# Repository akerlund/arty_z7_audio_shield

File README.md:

# arty_z7_audio_shield

Stereo audio IF with a Cirrus CS4272 24-bit codec IC.
Designed to be placed as a shield on the Arty Z7 FPGA board.
Has a 20-pin connector for the "mixer interface", i.e., a PCB with sliders and encoders.

First test (verison1) failed, the +-5V booster (bottom left in pic) operates incorrecty and
eats a lot of current, causing the 3.3V supply down to 0.8V.

Forgot the exposed thermal pad under that IC, too. Fixed with some copper tape, but might correlate?

Next step is to try a new design, i.e., another booster.

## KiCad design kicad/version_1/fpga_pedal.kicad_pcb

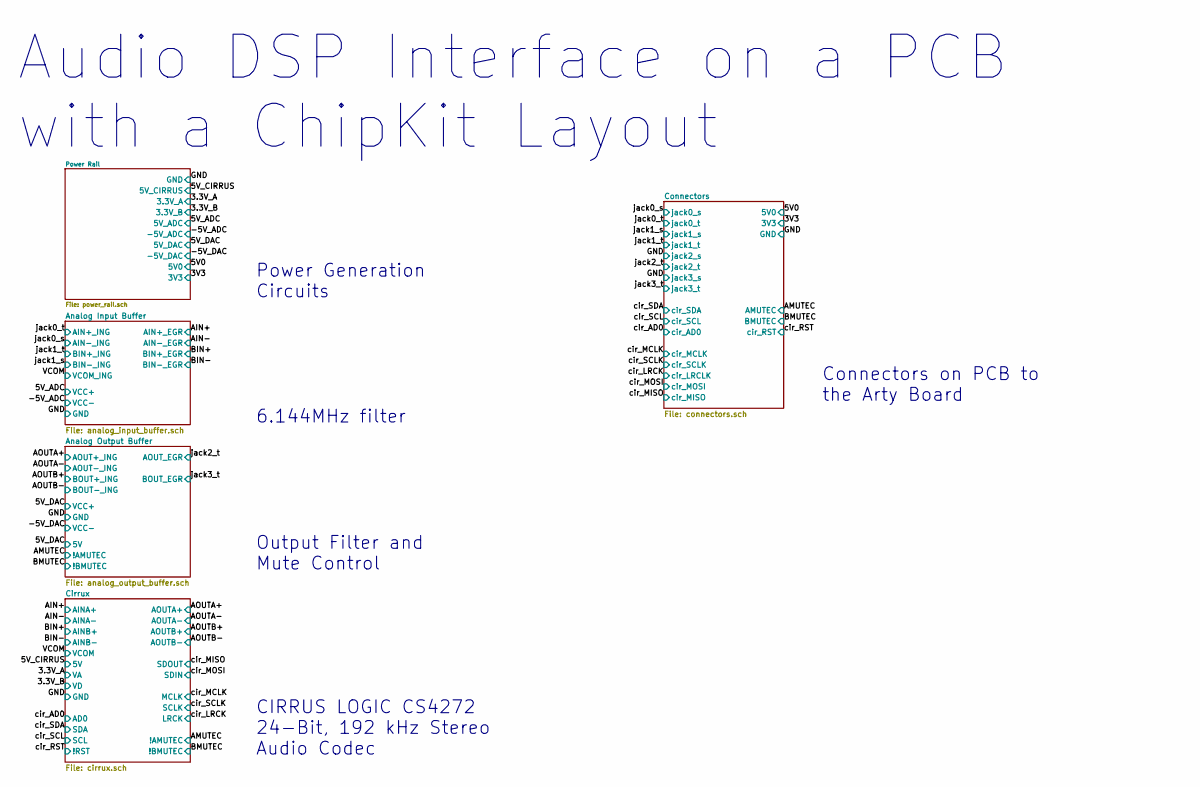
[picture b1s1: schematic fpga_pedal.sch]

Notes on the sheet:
CIRRUS LOGIC CS4272 24-Bit, 192 kHz Stereo Audio Codec
6.144MHz filter
Output Filter and Mute Control
Power Generation Circuits
Connectors on PCB to the Arty Board
Audio DSP Interface on a PCB with a ChipKit Layout

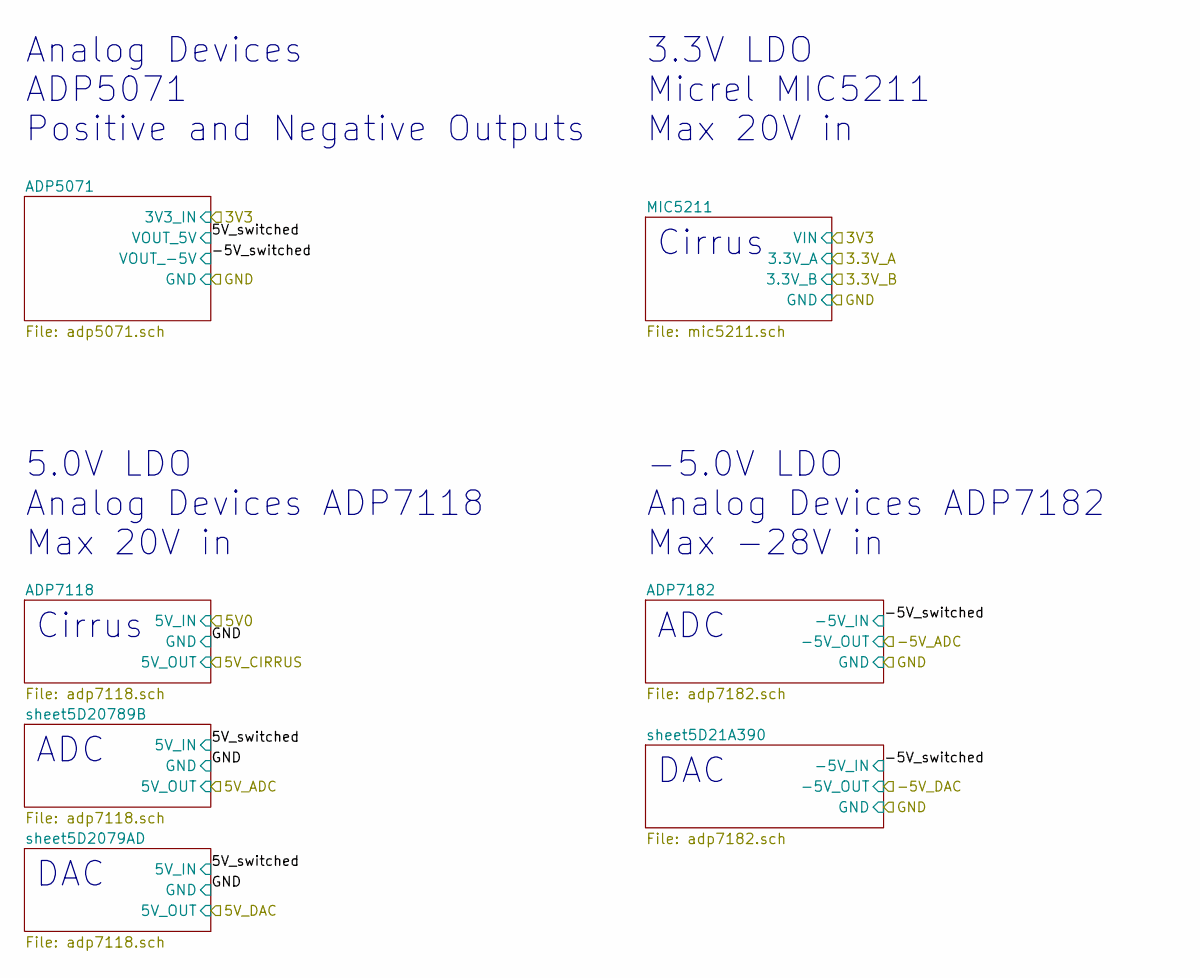
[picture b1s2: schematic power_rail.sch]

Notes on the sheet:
3.3V LDO Micrel MIC5211 Max 20V in
5.0V LDO Analog Devices ADP7118 Max 20V in
-5.0V LDO Analog Devices ADP7182 Max -28V in
Analog Devices ADP5071 Positive and Negative Outputs
ADC
Cirrus
DAC

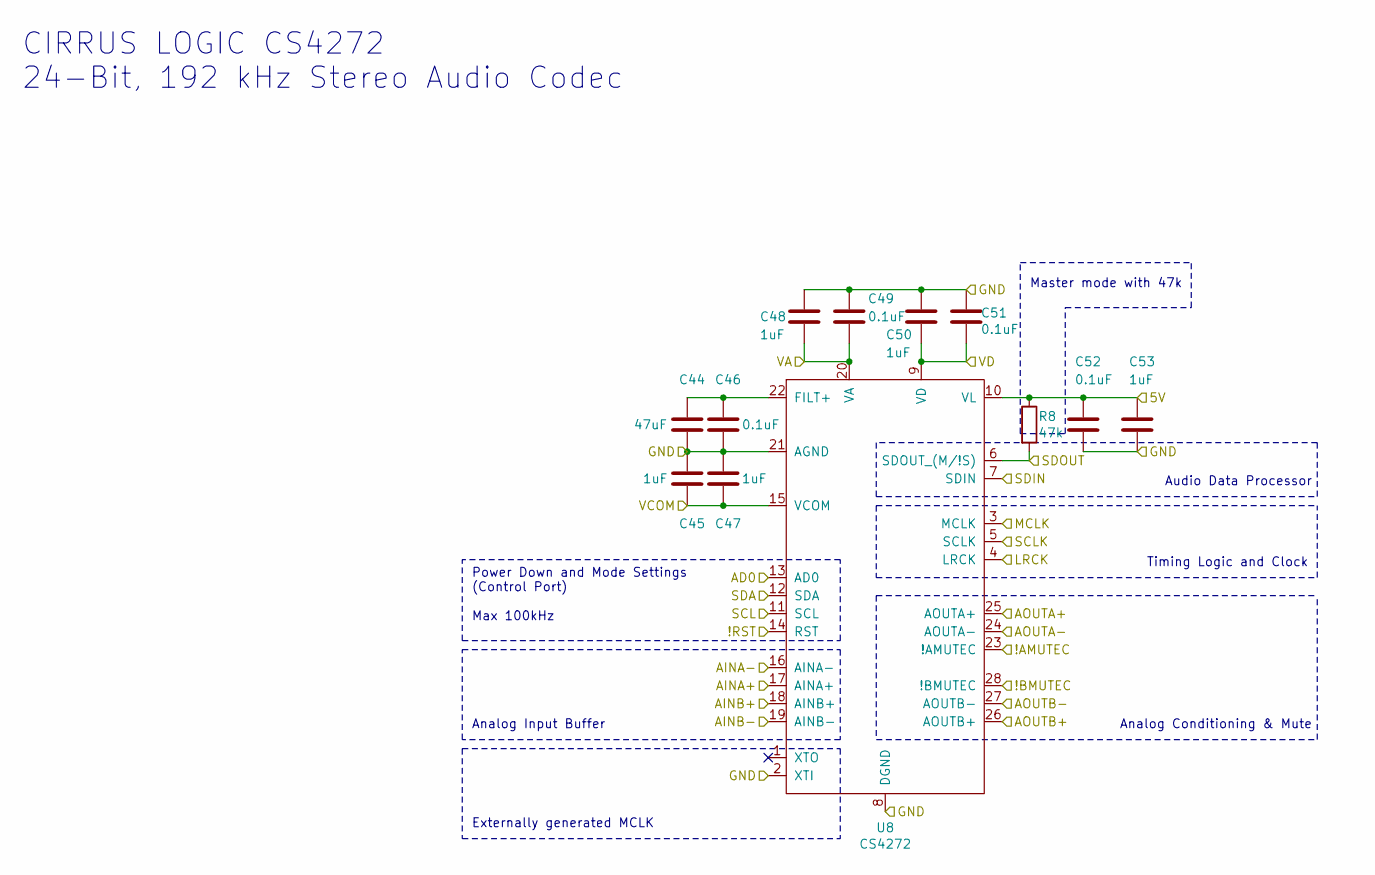
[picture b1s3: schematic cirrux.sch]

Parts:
C44: 47uF; C_1206_3216Metric_Pad1.42x1.75mm_HandSolder
C45, C47, C48, C50, C53: 1uF; C_0603_1608Metric_Pad1.05x0.95mm_HandSolder
C46, C49, C51, C52: 0.1uF; C_0603_1608Metric_Pad1.05x0.95mm_HandSolder
R8: 47k; R_0603_1608Metric_Pad1.05x0.95mm_HandSolder
U8: CS4272; TSSOP-28_4.4x9.7mm_P0.65mm

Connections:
/3.3V_A: C48.2, C49.2, U8.20 (VA); also elsewhere on the board
/3.3V_B: C50.2, C51.2, U8.9 (VD); also elsewhere on the board
/5V_CIRRUS: C52.1, C53.1, R8.1, U8.10 (VL); also elsewhere on the board
/AIN+: U8.17 (AINA+); also elsewhere on the board
/AIN-: U8.16 (AINA-); also elsewhere on the board
/AMUTEC: U8.23 (!AMUTEC); also elsewhere on the board
/AOUTA+: U8.25 (AOUTA+); also elsewhere on the board
/AOUTA-: U8.24 (AOUTA-); also elsewhere on the board
/AOUTB+: U8.26 (AOUTB+); also elsewhere on the board
/AOUTB-: U8.27 (AOUTB-); also elsewhere on the board
/BIN+: U8.18 (AINB+); also elsewhere on the board
/BIN-: U8.19 (AINB-); also elsewhere on the board
/BMUTEC: U8.28 (!BMUTEC); also elsewhere on the board
/GND: C44.2, C45.1, C46.2, C47.1, C48.1, C49.1, C50.1, C51.1, C52.2, C53.2, U8.2 (XTI), U8.8 (DGND), U8.21 (AGND); also elsewhere on the board
/VCOM: C45.2, C47.2, U8.15 (VCOM); also elsewhere on the board
/cir_AD0: U8.13 (AD0); also elsewhere on the board
/cir_LRCK: U8.4 (LRCK); also elsewhere on the board
/cir_MCLK: U8.3 (MCLK); also elsewhere on the board
/cir_MISO: R8.2, U8.6 (SDOUT_(M/!S)); also elsewhere on the board
/cir_MOSI: U8.7 (SDIN); also elsewhere on the board
/cir_RST: U8.14 (RST); also elsewhere on the board
/cir_SCL: U8.11 (SCL); also elsewhere on the board
/cir_SCLK: U8.5 (SCLK); also elsewhere on the board
/cir_SDA: U8.12 (SDA); also elsewhere on the board
unnamed: C44.1, C46.1, U8.22 (FILT+)

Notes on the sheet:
Analog Input Buffer
Power Down and Mode Settings (Control Port) Max 100kHz
Analog Conditioning & Mute
Timing Logic and Clock
Audio Data Processor
Master mode with 47k
Externally generated MCLK
CIRRUS LOGIC CS4272 24-Bit, 192 kHz Stereo Audio Codec

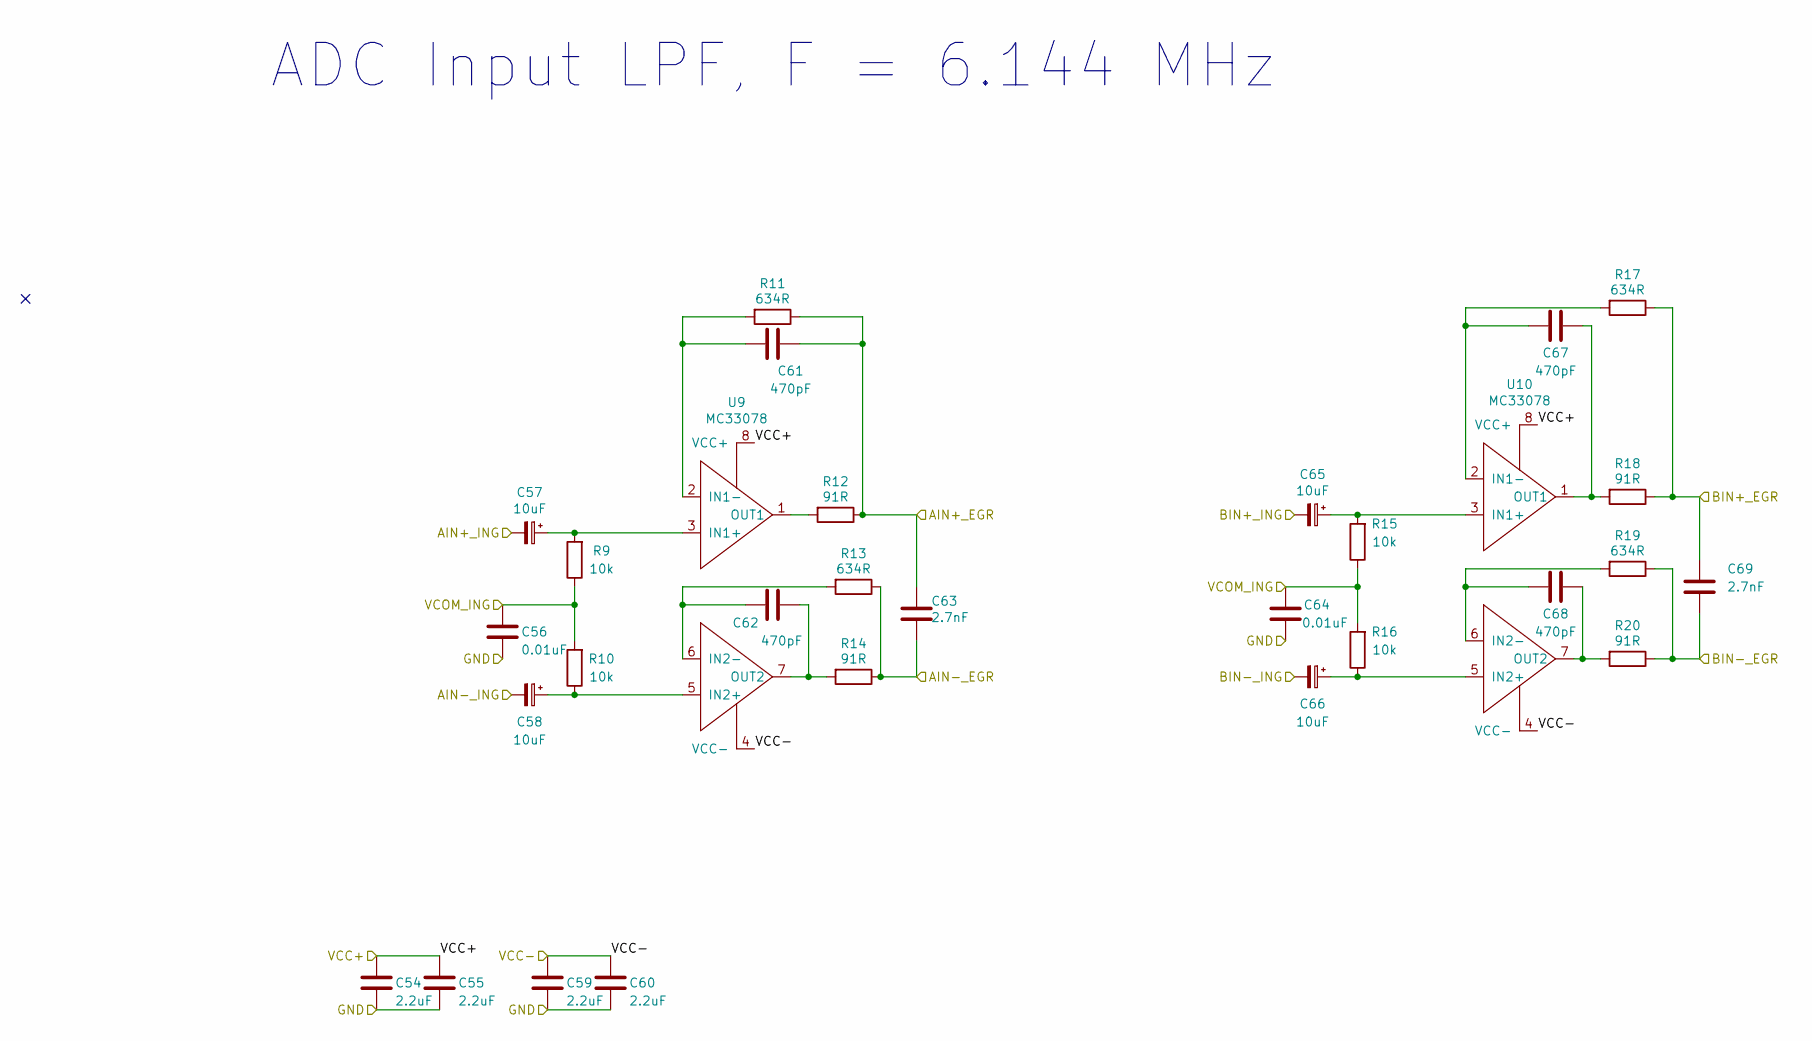
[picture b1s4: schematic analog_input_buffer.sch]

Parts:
C54, C55, C59, C60: 2.2uF; C_0603_1608Metric_Pad1.05x0.95mm_HandSolder
C56, C64: 0.01uF; C_0603_1608Metric_Pad1.05x0.95mm_HandSolder
C57, C58, C65, C66: 10uF; CP_Elec_4x5.7
C61, C62, C67, C68: 470pF; C_0603_1608Metric_Pad1.05x0.95mm_HandSolder
C63, C69: 2.7nF; C_0603_1608Metric_Pad1.05x0.95mm_HandSolder
R9, R10, R15, R16: 10k; R_0603_1608Metric_Pad1.05x0.95mm_HandSolder
R11, R13, R17, R19: 634R; R_0603_1608Metric_Pad1.05x0.95mm_HandSolder
R12, R14, R18, R20: 91R; R_0603_1608Metric_Pad1.05x0.95mm_HandSolder
U9, U10: MC33078; SOIC-8_3.9x4.9mm_P1.27mm

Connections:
/5V_ADC: C54.2, C55.2, U9.8 (VCC+), U10.8 (VCC+); also elsewhere on the board
/-5V_ADC: C59.2, C60.2, U9.4 (VCC-), U10.4 (VCC-); also elsewhere on the board
/AIN+: C61.1, C63.2, R11.1, R12.1; also elsewhere on the board
/AIN-: C63.1, R13.1, R14.1; also elsewhere on the board
/BIN+: C69.2, R17.1, R18.1; also elsewhere on the board
/BIN-: C69.1, R19.1, R20.1; also elsewhere on the board
/GND: C54.1, C55.1, C56.1, C59.1, C60.1, C64.1; also elsewhere on the board
/VCOM: C56.2, C64.2, R9.1, R10.2, R15.1, R16.2; also elsewhere on the board
/jack0_s: C58.2; also elsewhere on the board
/jack0_t: C57.2; also elsewhere on the board
/jack1_s: C66.2; also elsewhere on the board
/jack1_t: C65.2; also elsewhere on the board
unnamed: C57.1, R9.2, U9.3 (IN1+)
unnamed: C58.1, R10.1, U9.5 (IN2+)
unnamed: C61.2, R11.2, U9.2 (IN1-)
unnamed: C62.1, R14.2, U9.7 (OUT2)
unnamed: C62.2, R13.2, U9.6 (IN2-)
unnamed: C65.1, R15.2, U10.3 (IN1+)
unnamed: C66.1, R16.1, U10.5 (IN2+)
unnamed: C67.1, R18.2, U10.1 (OUT1)
unnamed: C67.2, R17.2, U10.2 (IN1-)
unnamed: C68.1, R20.2, U10.7 (OUT2)
unnamed: C68.2, R19.2, U10.6 (IN2-)
unnamed: R12.2, U9.1 (OUT1)

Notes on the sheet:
ADC Input LPF, F = 6.144 MHz

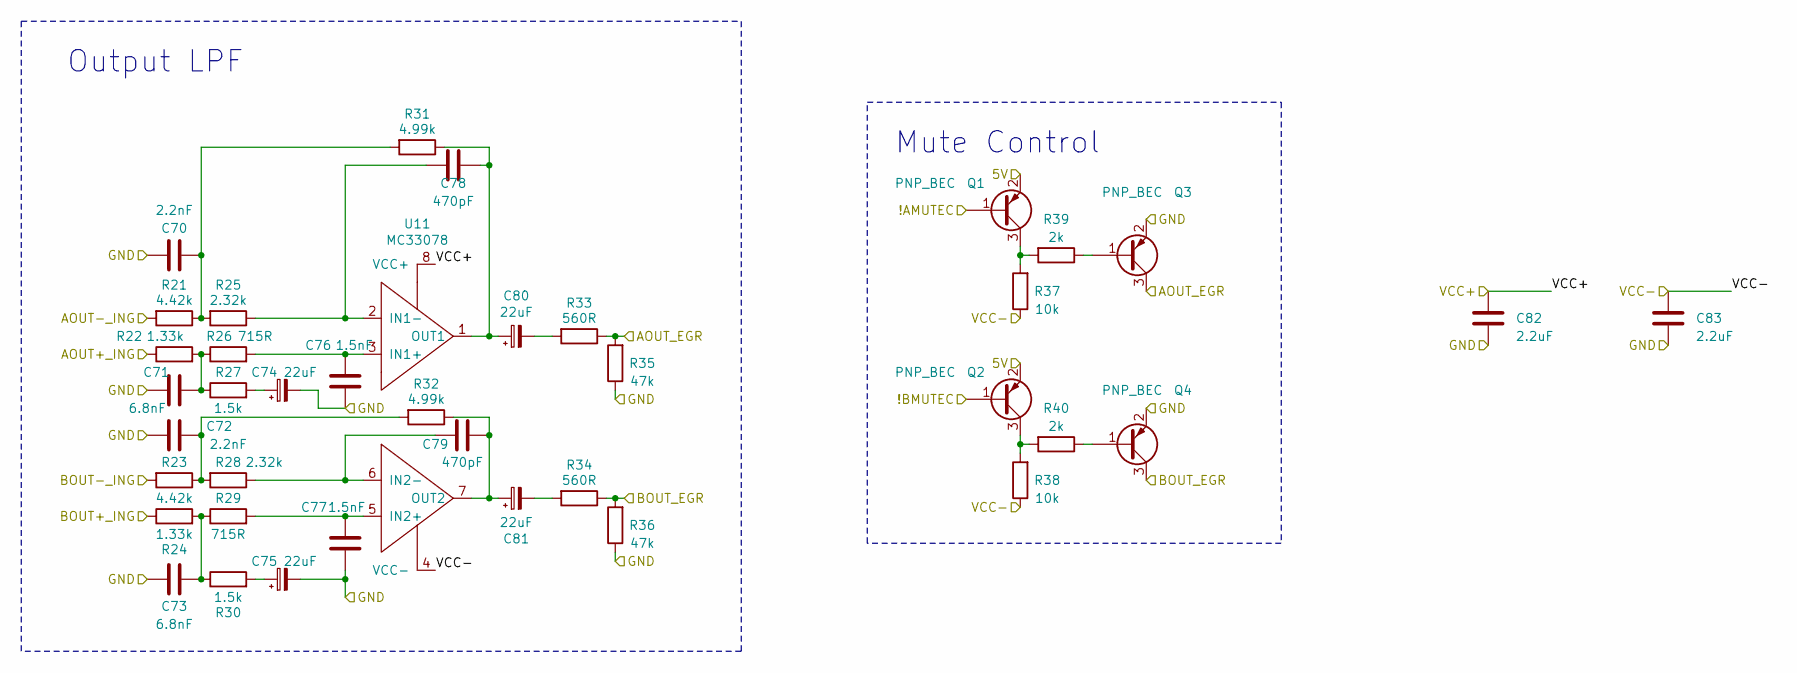
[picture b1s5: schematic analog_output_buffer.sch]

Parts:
C70, C72: 2.2nF; C_0603_1608Metric_Pad1.05x0.95mm_HandSolder
C71, C73: 6.8nF; C_0603_1608Metric_Pad1.05x0.95mm_HandSolder
C74, C75, C80, C81: 22uF; CP_Elec_5x5.7
C76, C77: 1.5nF; C_0603_1608Metric_Pad1.05x0.95mm_HandSolder
C78, C79: 470pF; C_0603_1608Metric_Pad1.05x0.95mm_HandSolder
C82, C83: 2.2uF; C_0603_1608Metric_Pad1.05x0.95mm_HandSolder
Q1, Q2, Q3, Q4: PNP_BEC; SOT-23
R21, R23: 4.42k; R_0603_1608Metric_Pad1.05x0.95mm_HandSolder
R22, R24: 1.33k; R_0603_1608Metric_Pad1.05x0.95mm_HandSolder
R25, R28: 2.32k; R_0603_1608Metric_Pad1.05x0.95mm_HandSolder
R26, R29: 715R; R_0603_1608Metric_Pad1.05x0.95mm_HandSolder
R27, R30: 1.5k; R_0603_1608Metric_Pad1.05x0.95mm_HandSolder
R31, R32: 4.99k; R_0603_1608Metric_Pad1.05x0.95mm_HandSolder
R33, R34: 560R; R_0603_1608Metric_Pad1.05x0.95mm_HandSolder
R35, R36: 47k; R_0603_1608Metric_Pad1.05x0.95mm_HandSolder
R37, R38: 10k; R_0603_1608Metric_Pad1.05x0.95mm_HandSolder
R39, R40: 2k; R_0603_1608Metric_Pad1.05x0.95mm_HandSolder
U11: MC33078; SOIC-8_3.9x4.9mm_P1.27mm

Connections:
/5V_DAC: C82.2, Q1.2 (E), Q2.2 (E), U11.8 (VCC+); also elsewhere on the board
/-5V_DAC: C83.2, R37.1, R38.1, U11.4 (VCC-); also elsewhere on the board
/AMUTEC: Q1.1 (B); also elsewhere on the board
/AOUTA+: R22.1; also elsewhere on the board
/AOUTA-: R21.2; also elsewhere on the board
/AOUTB+: R24.1; also elsewhere on the board
/AOUTB-: R23.2; also elsewhere on the board
/BMUTEC: Q2.1 (B); also elsewhere on the board
/GND: C70.1, C71.2, C72.1, C73.2, C74.2, C75.2, C76.2, C77.1, C82.1, C83.1, Q3.2 (E), Q4.2 (E), R35.1, R36.1; also elsewhere on the board
/jack2_t: Q3.3 (C), R33.1, R35.2; also elsewhere on the board
/jack3_t: Q4.3 (C), R34.1, R36.2; also elsewhere on the board
unnamed: C70.2, R21.1, R25.2, R31.2
unnamed: C71.1, R22.2, R26.1, R27.1
unnamed: C72.2, R23.1, R28.2, R32.2
unnamed: C73.1, R24.2, R29.1, R30.1
unnamed: C74.1, R27.2
unnamed: C75.1, R30.2
unnamed: C76.1, R26.2, U11.3 (IN1+)
unnamed: C77.2, R29.2, U11.5 (IN2+)
unnamed: C78.1, C80.1, R31.1, U11.1 (OUT1)
unnamed: C78.2, R25.1, U11.2 (IN1-)
unnamed: C79.1, C81.1, R32.1, U11.7 (OUT2)
unnamed: C79.2, R28.1, U11.6 (IN2-)
unnamed: C80.2, R33.2
unnamed: C81.2, R34.2
unnamed: Q1.3 (C), R37.2, R39.2
unnamed: Q2.3 (C), R38.2, R40.2
unnamed: Q3.1 (B), R39.1
unnamed: Q4.1 (B), R40.1

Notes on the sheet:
Mute Control
Output LPF

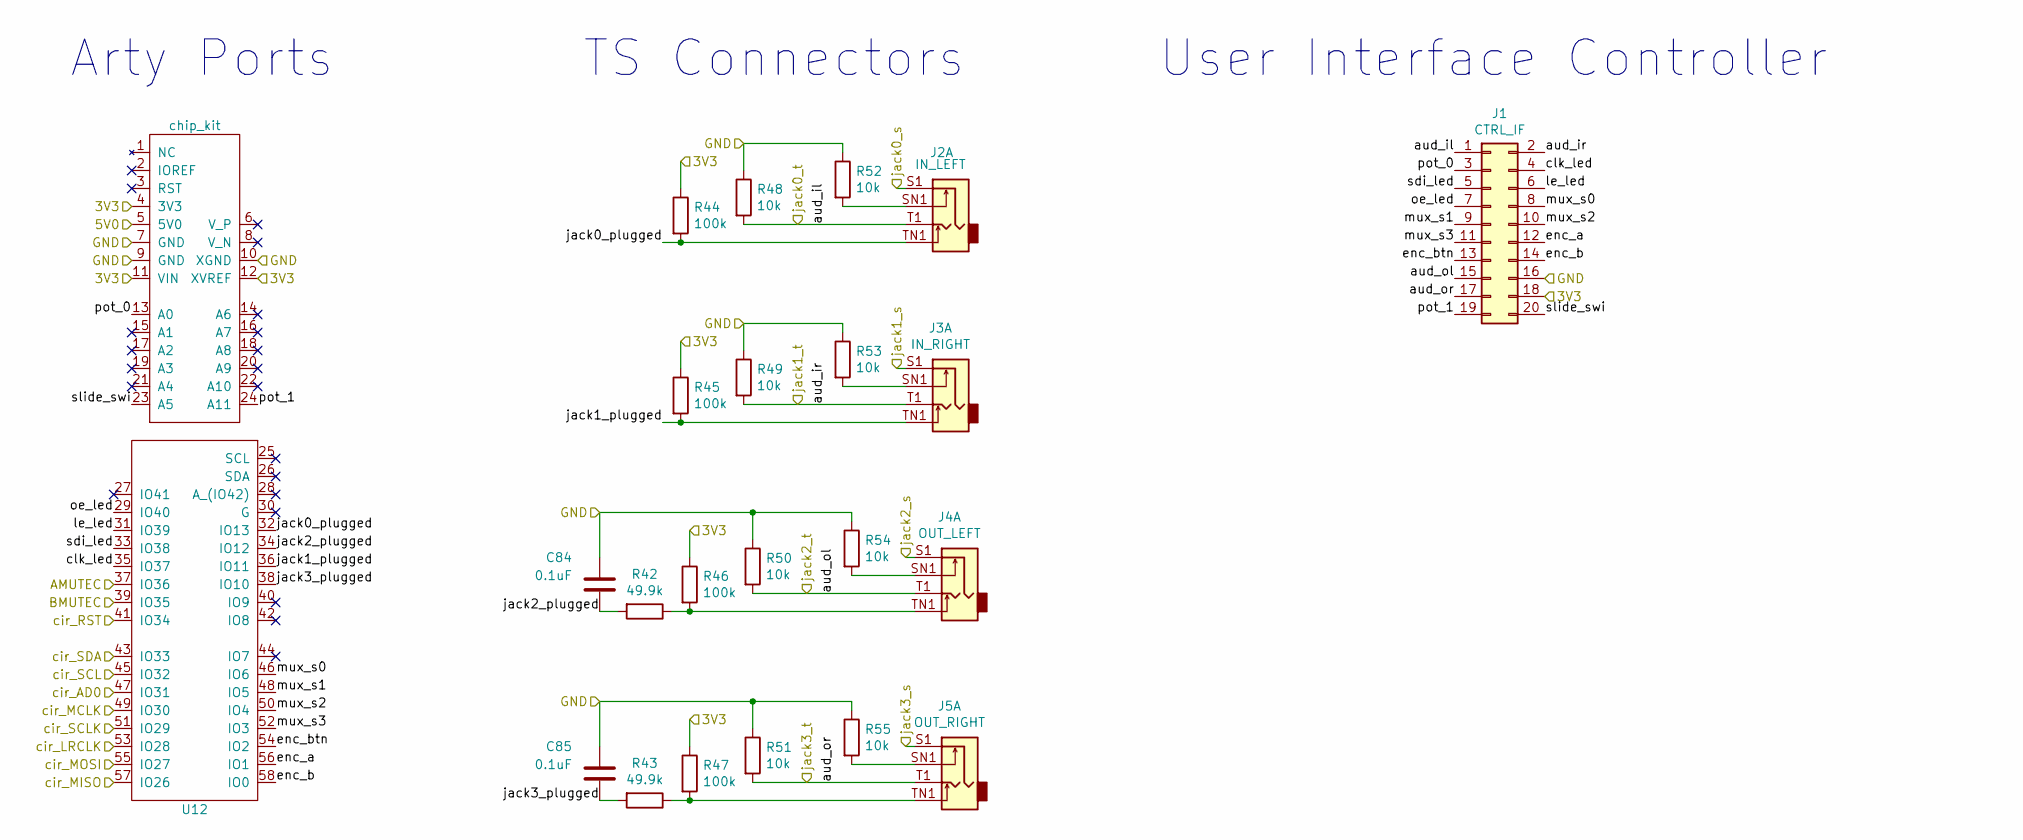
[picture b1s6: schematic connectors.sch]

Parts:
C84, C85: 0.1uF; C_0603_1608Metric_Pad1.05x0.95mm_HandSolder
J1: CTRL_IF; PinSocket_2x10_P2.54mm_Horizontal
J2: IN_LEFT; con_pcb_jack_mono_sw_6_3mm
J3: IN_RIGHT; con_pcb_jack_mono_sw_6_3mm
J4: OUT_LEFT; con_pcb_jack_mono_sw_6_3mm
J5: OUT_RIGHT; con_pcb_jack_mono_sw_6_3mm
R42, R43: 49.9k; R_0603_1608Metric_Pad1.05x0.95mm_HandSolder
R44, R45, R46, R47: 100k; R_0603_1608Metric_Pad1.05x0.95mm_HandSolder
R48, R49, R50, R51, R52, R53, R54, R55: 10k; R_0603_1608Metric_Pad1.05x0.95mm_HandSolder
U12: chip_kit; chipKIT

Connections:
/3V3: J1.18, R44.1, R45.1, R46.1, R47.1, U12.4 (3V3), U12.11 (VIN), U12.12 (XVREF); also elsewhere on the board
/5V0: U12.5 (5V0); also elsewhere on the board
/AMUTEC: U12.37 (IO36); also elsewhere on the board
/BMUTEC: U12.39 (IO35); also elsewhere on the board
/Connectors/clk_led: J1.4, U12.35 (IO37)
/Connectors/enc_a: J1.12, U12.56 (IO1)
/Connectors/enc_b: J1.14, U12.58 (IO0)
/Connectors/enc_btn: J1.13, U12.54 (IO2)
/Connectors/jack0_plugged: J2.TN1, R44.2, U12.32 (IO13)
/Connectors/jack1_plugged: J3.TN1, R45.2, U12.36 (IO11)
/Connectors/jack2_plugged: C84.2, R42.2, U12.34 (IO12)
/Connectors/jack3_plugged: C85.2, R43.2, U12.38 (IO10)
/Connectors/le_led: J1.6, U12.31 (IO39)
/Connectors/mux_s0: J1.8, U12.46 (IO6)
/Connectors/mux_s1: J1.9, U12.48 (IO5)
/Connectors/mux_s2: J1.10, U12.50 (IO4)
/Connectors/mux_s3: J1.11, U12.52 (IO3)
/Connectors/oe_led: J1.7, U12.29 (IO40)
/Connectors/pot_0: J1.3, U12.13 (A0)
/Connectors/pot_1: J1.19, U12.24 (A11)
/Connectors/sdi_led: J1.5, U12.33 (IO38)
/Connectors/slide_swi: J1.20, U12.23 (A5)
/GND: C84.1, C85.1, J1.16, J4.S1, J5.S1, R48.1, R49.1, R50.1, R51.1, R52.1, R53.1, R54.1, R55.1, U12.7 (GND), U12.9 (GND), U12.10 (XGND); also elsewhere on the board
/cir_AD0: U12.47 (IO31); also elsewhere on the board
/cir_LRCK: U12.53 (IO28); also elsewhere on the board
/cir_MCLK: U12.49 (IO30); also elsewhere on the board
/cir_MISO: U12.57 (IO26); also elsewhere on the board
/cir_MOSI: U12.55 (IO27); also elsewhere on the board
/cir_RST: U12.41 (IO34); also elsewhere on the board
/cir_SCL: U12.45 (IO32); also elsewhere on the board
/cir_SCLK: U12.51 (IO29); also elsewhere on the board
/cir_SDA: U12.43 (IO33); also elsewhere on the board
/jack0_s: J2.S1; also elsewhere on the board
/jack0_t: J1.1, J2.T1, R48.2; also elsewhere on the board
/jack1_s: J3.S1; also elsewhere on the board
/jack1_t: J1.2, J3.T1, R49.2; also elsewhere on the board
/jack2_t: J1.15, J4.T1, R50.2; also elsewhere on the board
/jack3_t: J1.17, J5.T1, R51.2; also elsewhere on the board
unnamed: J2.SN1, R52.2
unnamed: J3.SN1, R53.2
unnamed: J4.SN1, R54.2
unnamed: J4.TN1, R42.1, R46.2
unnamed: J5.SN1, R55.2
unnamed: J5.TN1, R43.1, R47.2

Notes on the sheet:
Arty Ports
TS Connectors
User Interface Controller

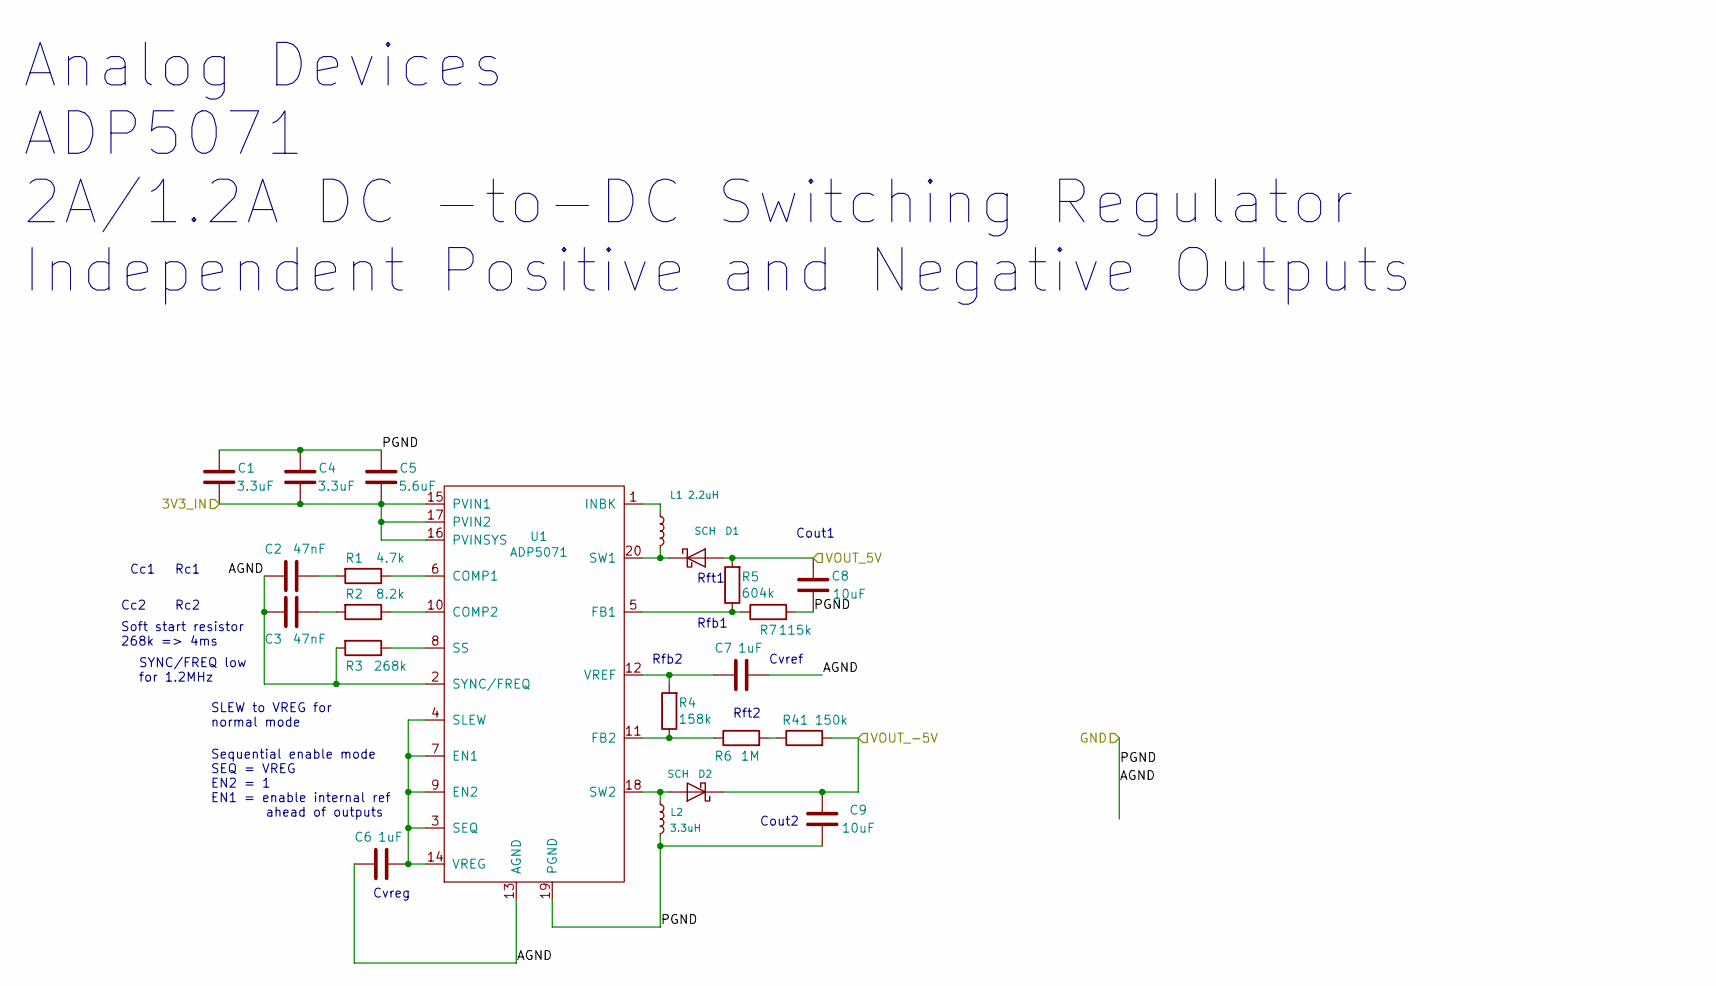
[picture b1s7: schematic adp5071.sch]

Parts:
C1, C4: 3.3uF; C_1206_3216Metric_Pad1.42x1.75mm_HandSolder
C2, C3: 47nF; C_0603_1608Metric_Pad1.05x0.95mm_HandSolder
C5: 5.6uF; C_1206_3216Metric_Pad1.42x1.75mm_HandSolder
C6, C7: 1uF; C_0603_1608Metric_Pad1.05x0.95mm_HandSolder
C8, C9: 10uF; C_1210_3225Metric_Pad1.42x2.65mm_HandSolder
D1, D2: SCH; D_SOD-123
L1: 2.2uH; L_Coilcraft_XxL4040
L2: 3.3uH; L_Coilcraft_XxL4040
R1: 4.7k; R_0603_1608Metric_Pad1.05x0.95mm_HandSolder
R2: 8.2k; R_0603_1608Metric_Pad1.05x0.95mm_HandSolder
R3: 268k; R_0603_1608Metric_Pad1.05x0.95mm_HandSolder
R4: 158k; R_0603_1608Metric_Pad1.05x0.95mm_HandSolder
R5: 604k; R_0603_1608Metric_Pad1.05x0.95mm_HandSolder
R6: 1M; R_0603_1608Metric_Pad1.05x0.95mm_HandSolder
R7: 115k; R_0603_1608Metric_Pad1.05x0.95mm_HandSolder
R41: 150k; R_0603_1608Metric_Pad1.05x0.95mm_HandSolder
U1: ADP5071; TSSOP-20_4.4x6.5mm_P0.65mm

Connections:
/3V3: C1.1, C4.1, C5.1, U1.15 (PVIN1), U1.16 (PVINSYS), U1.17 (PVIN2); also elsewhere on the board
/GND: C1.2, C2.2, C3.2, C4.2, C5.2, C6.2, C7.1, C8.1, C9.1, L2.2, R3.2, R7.2, U1.2 (SYNC/FREQ), U1.13 (AGND), U1.19 (PGND); also elsewhere on the board
/Power Rail/5V_switched: C8.2, D1.2 (A), R5.2; also elsewhere on the board
/Power Rail/-5V_switched: C9.2, D2.1 (K), R41.2; also elsewhere on the board
unnamed: C2.1, R1.2
unnamed: C3.1, R2.2
unnamed: C6.1, U1.3 (SEQ), U1.4 (SLEW), U1.7 (EN1), U1.9 (EN2), U1.14 (VREG)
unnamed: C7.2, R4.2, U1.12 (VREF)
unnamed: D1.1 (K), L1.2, U1.20 (SW1)
unnamed: D2.2 (A), L2.1, U1.18 (SW2)
unnamed: L1.1, U1.1 (INBK)
unnamed: R1.1, U1.6 (COMP1)
unnamed: R2.1, U1.10 (COMP2)
unnamed: R3.1, U1.8 (SS)
unnamed: R4.1, R6.1, U1.11 (FB2)
unnamed: R5.1, R7.1, U1.5 (FB1)
unnamed: R6.2, R41.1

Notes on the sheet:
Analog Devices ADP5071 2A/1.2A DC -to-DC Switching Regulator Independent Positive and Negative Outputs
Rft1
Rfb1
Rft2
Rfb2
Cout1
Cout2
Cvref
Rc1
Rc2
Cc1
Cc2
Cvreg
Soft start resistor 268k => 4ms
Sequential enable mode SEQ = VREG EN2 = 1 EN1 = enable internal ref ahead of outputs
SYNC/FREQ low for 1.2MHz
SLEW to VREG for normal mode

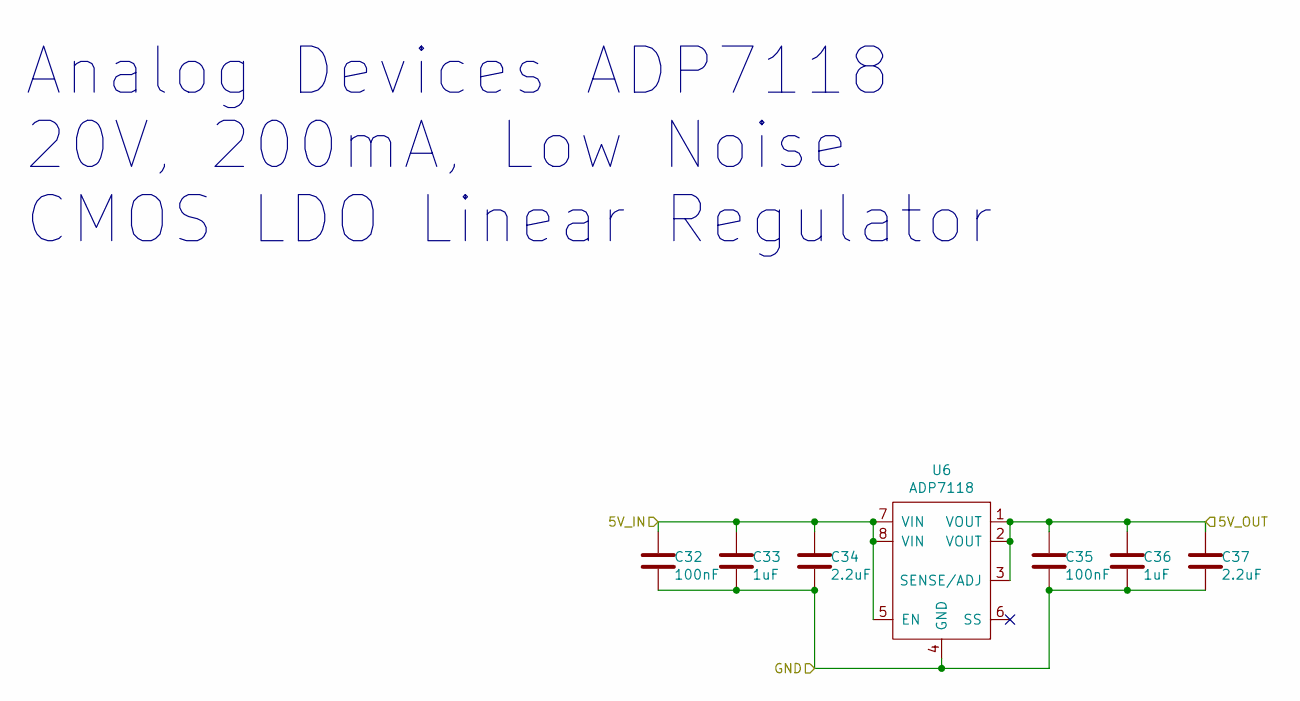
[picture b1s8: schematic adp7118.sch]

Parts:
C10, C13: 100nF; C_0603_1608Metric_Pad1.05x0.95mm_HandSolder
C11, C14: 1uF; C_0603_1608Metric_Pad1.05x0.95mm_HandSolder
C12, C15: 2.2uF; C_0603_1608Metric_Pad1.05x0.95mm_HandSolder
U2: ADP7118; SOIC-8_3.9x4.9mm_P1.27mm

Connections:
/5V0: C10.1, C11.1, C12.1, U2.5 (EN), U2.7 (VIN), U2.8 (VIN); also elsewhere on the board
/5V_CIRRUS: C13.1, C14.1, C15.1, U2.1 (VOUT), U2.2 (VOUT), U2.3 (SENSE/ADJ); also elsewhere on the board
/GND: C10.2, C11.2, C12.2, C13.2, C14.2, C15.2, U2.4 (GND); also elsewhere on the board

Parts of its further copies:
C26, C29, C32, C35: 100nF; C_0603_1608Metric_Pad1.05x0.95mm_HandSolder
C27, C30, C33, C36: 1uF; C_0603_1608Metric_Pad1.05x0.95mm_HandSolder
C28, C31, C34, C37: 2.2uF; C_0603_1608Metric_Pad1.05x0.95mm_HandSolder
U5, U6: ADP7118; SOIC-8_3.9x4.9mm_P1.27mm

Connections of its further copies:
/5V_ADC: C29.1, C30.1, C31.1, U5.1 (VOUT), U5.2 (VOUT), U5.3 (SENSE/ADJ); also elsewhere on the board
/5V_DAC: C35.1, C36.1, C37.1, U6.1 (VOUT), U6.2 (VOUT), U6.3 (SENSE/ADJ); also elsewhere on the board
/GND: C26.2, C27.2, C28.2, C29.2, C30.2, C31.2, C32.2, C33.2, C34.2, C35.2, C36.2, C37.2, U5.4 (GND), U6.4 (GND); also elsewhere on the board
/Power Rail/5V_switched: C26.1, C27.1, C28.1, C32.1, C33.1, C34.1, U5.5 (EN), U5.7 (VIN), U5.8 (VIN), U6.5 (EN), U6.7 (VIN), U6.8 (VIN); also elsewhere on the board

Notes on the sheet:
Analog Devices ADP7118 20V, 200mA, Low Noise CMOS LDO Linear Regulator

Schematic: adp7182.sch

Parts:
C16, C21: 100nF; C_0603_1608Metric_Pad1.05x0.95mm_HandSolder
C17, C20: 1nF; C_0603_1608Metric_Pad1.05x0.95mm_HandSolder
C18, C19: 2.2uF; CP_Elec_4x5.7
U3: ADP7182; SOT-23-5

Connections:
/-5V_ADC: C19.2, C20.1, C21.1, U3.5 (VOUT); also elsewhere on the board
/GND: C16.2, C17.2, C18.1, C19.1, C20.2, C21.2, U3.1 (GND); also elsewhere on the board
/Power Rail/-5V_switched: C16.1, C17.1, C18.2, U3.2 (VIN), U3.3 (EN); also elsewhere on the board

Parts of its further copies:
C38, C43: 100nF; C_0603_1608Metric_Pad1.05x0.95mm_HandSolder
C39, C42: 1nF; C_0603_1608Metric_Pad1.05x0.95mm_HandSolder
C40, C41: 2.2uF; CP_Elec_4x5.7
U7: ADP7182; SOT-23-5

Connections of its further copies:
/-5V_DAC: C41.2, C42.1, C43.1, U7.5 (VOUT); also elsewhere on the board
/GND: C38.2, C39.2, C40.1, C41.1, C42.2, C43.2, U7.1 (GND); also elsewhere on the board
/Power Rail/-5V_switched: C38.1, C39.1, C40.2, U7.2 (VIN), U7.3 (EN); also elsewhere on the board

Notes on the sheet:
Analog Devices ADP7182 –28 V, −200 mA, Low Noise,Linear Regulator

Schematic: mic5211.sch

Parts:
C22, C24, C25: 1uF; C_0603_1608Metric_Pad1.05x0.95mm_HandSolder
C23: 100nF; C_0603_1608Metric_Pad1.05x0.95mm_HandSolder
U4: MIC5211; SOT-23-6

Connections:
/3.3V_A: C24.1, U4.6 (VOUTA); also elsewhere on the board
/3.3V_B: C25.2, U4.4 (VOUTB); also elsewhere on the board
/3V3: C22.1, C23.1, U4.1 (EN_A), U4.3 (EN_B), U4.5 (VIN); also elsewhere on the board
/GND: C22.2, C23.2, C24.2, C25.1, U4.2 (GND); also elsewhere on the board

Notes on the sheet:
Dual μCap 80mA LDO Regulator
